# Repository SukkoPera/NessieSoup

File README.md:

# NessieSoup
NessieSoup is a simple adapter that allows connecting Super Nintendo controllers to a Commodore 64, 128 or Plus/4.

## Summary
The game [Attack of the PETSCII Robots](https://www.the8bitguy.com/product/petscii-robots/) by The 8-Bit Guy supports SNES controllers when running on the C64, VIC-20, Plus/4, and PET with a custom adapter. While I didn't have the game (nor the adapter), I was able to figure out how it works and I noticed that it could easily be expanded to support more than one controller and advanced peripherals, such as the *SNES MultiTap* and (possibly) the [Super Scope](https://en.wikipedia.org/wiki/Super_Scope).

So I designed a new PCB with 2 controllers ports: the first port is designed to be fully compatible with the original adapter (which means it should work with PETSCII Robots, but I was unable to test it), while the second one supports either a second controller or the more advanced peripherals.

The project also has the purpose of openly documenting this adapter, so that more games can be developed with support for SNES controllers (and all their buttons!).

The board plugs in the User Port, which means that it can also be used on a C16 or C116 through [a User Port card](https://github.com/SukkoPera/16up).

## Assembly
Get the SNES and userport connectors on AliExpress & similar sites.

The capacitor is optional.

## Programming
The board is completely passive, so it's all down to the software. This means you should first of all get familiar with the [SNES controller protocol](https://github.com/SukkoPera/NessieSoup/wiki/Super-Nintendo-Entertainment-System:-Pinouts-&-Protocol), then the following will start to make sense:

|Signal     |Userport Pin +4|Userport Pin C64/128|Userport Pin VIC-20|Userport Pin PET|
|-----------|---------------|--------------------|-------------------|----------------|
|Latch      |J/D6           |J/PB5               |J/PB5              |J/PA5           |
|Clock      |F/D7           |F/PB3               |F/PB3              |F/PA3           |
|D0 (Port 1)|K/D1           |K/PB6               |K/PB6              |K/PA6           |
|D0 (Port 2)|B/D0           |C/PB0               |C/PB0              |C/PB0           |
|D1 (Port 2)|4/D2           |                    |                   |                |
|PP (Port 2)|5/D3           |                    |                   |                |

*NOTE: The adapter has only been tested on the +4 and C64, pinouts for other computers is only provided as a reference, use at your own risk.*

Note that JP1 must be set to **+4** only when the board is connected to a +4, C16 or C116 computer, use the **C64** position in all other cases.

Some example code for controller detection and polling is provided on the [Wiki](https://github.com/SukkoPera/NessieSoup/wiki).

Code for reading the SNES MultiTap and the Super Scope has not been developed yet. The *D1* and *PP* signals are only needed for these purposes and the way they are connected might only work on the +4. More work is needed in this regard, feel free to contribute ;).

## Releases
If you want to get this board produced, you are recommended to get [the latest release](https://github.com/SukkoPera/NessieSoup/releases) rather than the current git version, as the latter might be under development and is not guaranteed to be working.

Every release is accompanied by its Bill Of Materials (BOM) file and any relevant notes about it, which you are recommended to read carefully.

## License
The NessieSoup documentation, including the design itself, is copyright &copy; SukkoPera 2024 and is licensed under the [Creative Commons Attribution-NonCommercial-ShareAlike 4.0 International License](https://creativecommons.org/licenses/by-nc-sa/4.0/).

This documentation is distributed *as is* and WITHOUT ANY EXPRESS OR IMPLIED WARRANTIES whatsoever with respect to its functionality, operability or use, including, without limitation, any implied warranties OF MERCHANTABILITY, SATISFACTORY QUALITY, FITNESS FOR A PARTICULAR PURPOSE or infringement. We expressly disclaim any liability whatsoever for any direct, indirect, consequential, incidental or special damages, including, without limitation, lost revenues, lost profits, losses resulting from business interruption or loss of data, regardless of the form of action or legal theory under which the liability may be asserted, even if advised of the possibility or likelihood of such damages.

## Support the Project
If you want to get some boards manufactured, you can get them from PCBWay through this link:

You get my gratitude and cheap, professionally-made and good quality PCBs, I get some credit that will help with this and [other projects](https://www.pcbway.com/project/member/shareproject/?bmbid=41100). You won't even have to worry about the various PCB options, it's all pre-configured for you!

Also, if you still have to register, [you can use this link](https://www.pcbway.com/setinvite.aspx?inviteid=41100) to get some bonus initial credit (and yield me some more).

You can also buy me a coffee if you want:

## Thanks
* The 8-Bit Guy for designing the original adapter.
* wepfont for the [M Malaming](https://www.fontspace.com/m-malaming-font-f118544) font used in the logo.

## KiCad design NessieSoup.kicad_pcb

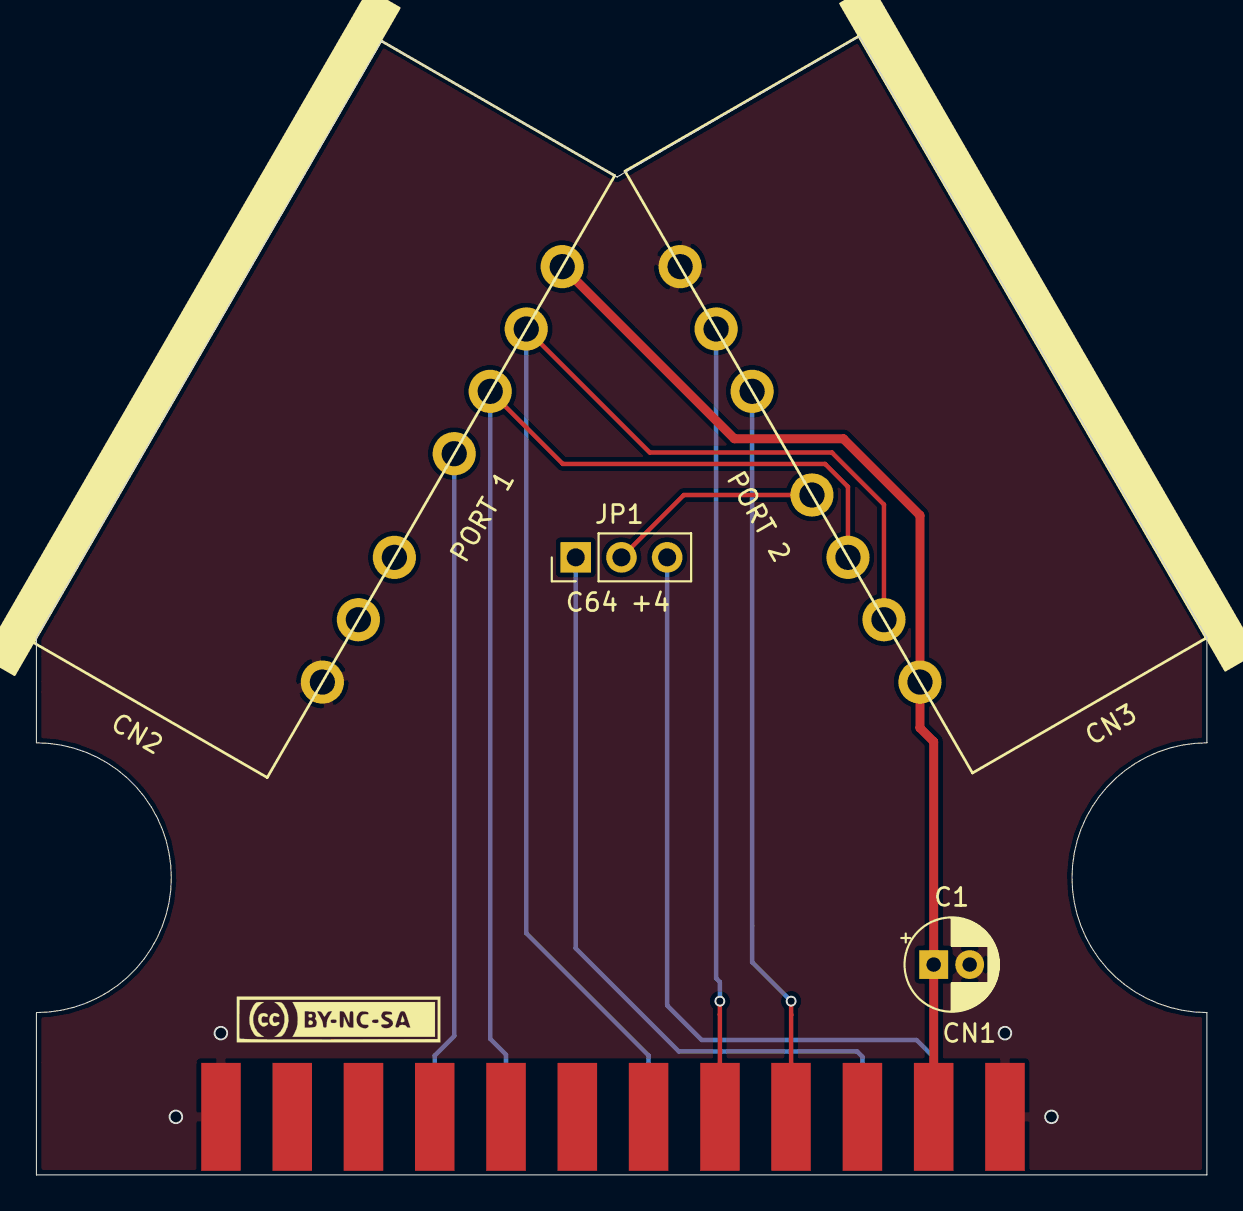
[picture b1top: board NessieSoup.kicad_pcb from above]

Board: 2 copper layers, 65.0 x 63.2 mm, 8 parts (0 on the bottom side), 10 nets.

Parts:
C1: 47u; CP_Radial_D5.0mm_P2.00mm
CN1: PLUS4_USERPORT; UserPortFemale
CN2: CONN_SNES_1; CONN_SNES
CN3: CONN_SNES_2; CONN_SNES
JP1: JMP_16_64; PinHeader_1x03_P2.54mm_Vertical
V0: LICENSE; cc_by_nc_sa_small
V1: LOGO1; Logo1
V2: LOGO2; Logo2

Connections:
+5V: C1.1, CN1.2, CN2.7, CN3.7
/clock: CN1.F, CN2.6, CN3.6
/latch: CN1.J, CN2.5, CN3.5
/port1_d0: CN1.K, CN2.4
/port2_d0: CN3.4, JP1.2
/port2_d1: CN1.4, CN3.3
/port2_pp: CN1.5, CN3.2
GND: C1.2, CN1.1, CN1.12, CN1.A, CN1.N, CN2.1, CN3.1
unnamed: CN1.B, JP1.3
unnamed: CN1.C, JP1.1

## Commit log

2024-07-08 Almost there
2024-07-08 Add capacitor Yeah, we must have at least one component...
2024-07-09 Refine shape
2024-07-09 Add +4/C64 switch
2025-01-01 Add renders and update README

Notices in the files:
NessieSoup.kicad_pcb:
Licensed under CC BY-NC-SA 4.0
©2024 SukkoPera
